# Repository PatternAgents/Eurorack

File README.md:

# EuroRack
EuroRack Specifications and Reference Designs 

-----------------------------------------------------

There are many "patchable" audio synthesizers, including Moog, Buchla, Paia, and many more
from the 1970's and on. Many of those early systems were incompatible with each other,
using different voltage and control levels, so it was difficult to use them together.
Doepfer created the A-100 System, on which Eurorack is based, for a more open
framework where different manufacturers or designers could add modules to the
system to personalize it. EuroRack has become very popular for modular synthesizers. 

This repository contains Open Source Hardware Reference Designs for EuroRack (Legacy 1.0)
that anyone can use or fabricate for themselves.

If you would like to purchase pre-built and tested units,
please see our website at : [PatternAgents](https://patternagents.com/store)

-----------------------------------------------------

EuroRack References and Articles

[Doepfer-Creator](http://www.doepfer.de/a100_man/a100m_e.htm)

[Wikipedia-Doepfer](https://en.wikipedia.org/wiki/Doepfer_A-100)

[Patch Pierre](http://patchpierre.blogspot.com/2012/02/eurorack-standard.html)

[SDIY Info](https://www.sdiy.info/w/Eurorack)

-----------------------------------------------------

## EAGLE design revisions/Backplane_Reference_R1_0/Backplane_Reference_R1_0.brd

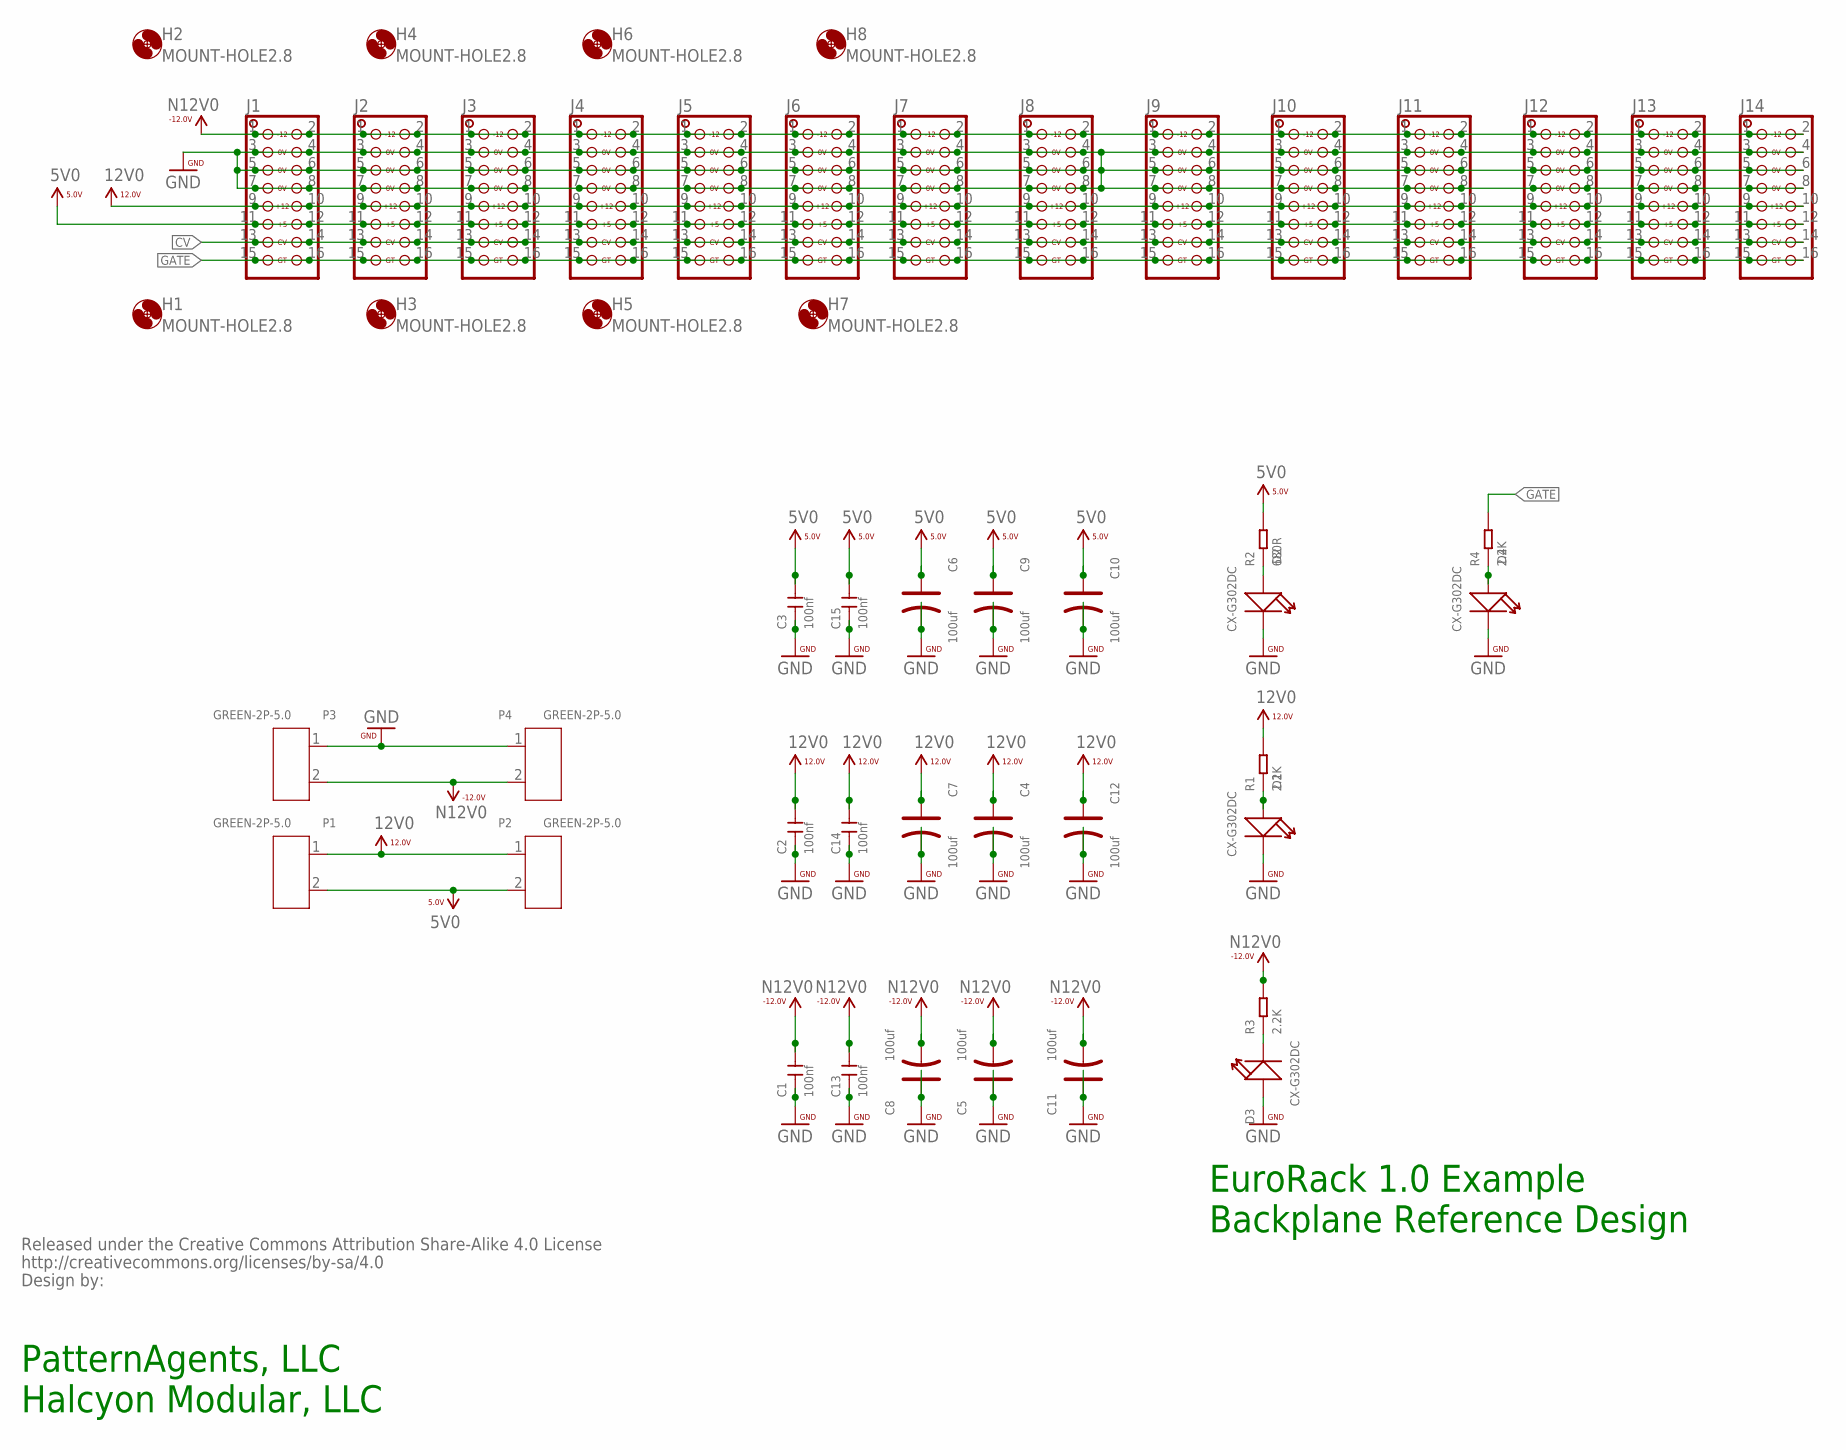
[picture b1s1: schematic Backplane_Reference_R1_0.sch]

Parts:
C1, C2, C3, C13, C14, C15: 100nf; CERAMIC-2.54
C4, C5, C6, C7, C8, C9, C10, C11, C12: 100uf; PC-D5.3MM
D1, D2, D3, D4: CX-G302DC; LED2-2.54-D3.0MM
H1, H2, H3, H4, H5, H6, H7, H8: MOUNT-HOLE2.8; 2,8
J1, J2, J3, J4, J5, J6, J7, J8, J9, J10, J11, J12, J13, J14: EUROPWR_2X08-SHROUD; 2X08_EUROPWR_SHROUD
P1, P2, P3, P4: GREEN-2P-5.0; H2-5.0-10.5X8.0MM
R1, R3, R4: 2.2K; PR-D2.3XL6.5MM
R2: 680R; PR-D2.3XL6.5MM
U$48: BY_CC_SA_TEXTTEXT; BY_CC_SA_TEXT

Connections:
5V0: C3.2, C6.+, C9.+, C10.+, C15.2, J1.11, J1.12, J2.11, J2.12, J3.11, J3.12, J4.11, J4.12, J5.11, J5.12, J6.11, J6.12, J7.11, J7.12, J8.11, J8.12, J9.11, J9.12, J10.11, J10.12, J11.11, J11.12, J12.11, J12.12, J13.11, J13.12, J14.11, J14.12, P1.2, P2.2, R2.2
12V0: C2.2, C4.+, C7.+, C12.+, C14.2, J1.9, J1.10, J2.9, J2.10, J3.9, J3.10, J4.9, J4.10, J5.9, J5.10, J6.9, J6.10, J7.9, J7.10, J8.9, J8.10, J9.9, J9.10, J10.9, J10.10, J11.9, J11.10, J12.9, J12.10, J13.9, J13.10, J14.9, J14.10, P1.1, P2.1, R1.2
CV: J1.13, J1.14, J2.13, J2.14, J3.13, J3.14, J4.13, J4.14, J5.13, J5.14, J6.13, J6.14, J7.13, J7.14, J8.13, J8.14, J9.13, J9.14, J10.13, J10.14, J11.13, J11.14, J12.13, J12.14, J13.13, J13.14, J14.13, J14.14
GATE: J1.15, J1.16, J2.15, J2.16, J3.15, J3.16, J4.15, J4.16, J5.15, J5.16, J6.15, J6.16, J7.15, J7.16, J8.15, J8.16, J9.15, J9.16, J10.15, J10.16, J11.15, J11.16, J12.15, J12.16, J13.15, J13.16, J14.15, J14.16, R4.2
GND: C1.1, C2.1, C3.1, C4.-, C5.+, C6.-, C7.-, C8.+, C9.-, C10.-, C11.+, C12.-, C13.1, C14.1, C15.1, D1.K (-), D2.K (-), D3.A (+), D4.K (-), J1.3, J1.4, J1.5, J1.6, J1.7, J1.8, J2.3, J2.4, J2.5, J2.6, J2.7, J2.8, J3.3, J3.4, J3.5, J3.6, J3.7, J3.8, J4.3, J4.4, J4.5, J4.6, J4.7, J4.8, J5.3, J5.4, J5.5, J5.6, J5.7, J5.8, J6.3, J6.4, J6.5, J6.6, J6.7, J6.8, J7.3, J7.4, J7.5, J7.6, J7.7, J7.8, J8.3, J8.4, J8.5, J8.6, J8.7, J8.8, J9.3, J9.4, J9.5, J9.6, J9.7, J9.8, J10.3, J10.4, J10.5, J10.6, J10.7, J10.8, J11.3, J11.4, J11.5, J11.6, J11.7, J11.8, J12.3, J12.4, J12.5, J12.6, J12.7, J12.8, J13.3, J13.4, J13.5, J13.6, J13.7, J13.8, J14.3, J14.4, J14.5, J14.6, J14.7, J14.8, P3.1, P4.1
N12V0: C1.2, C5.-, C8.-, C11.-, C13.2, J1.1, J1.2, J2.1, J2.2, J3.1, J3.2, J4.1, J4.2, J5.1, J5.2, J6.1, J6.2, J7.1, J7.2, J8.1, J8.2, J9.1, J9.2, J10.1, J10.2, J11.1, J11.2, J12.1, J12.2, J13.1, J13.2, J14.1, J14.2, P3.2, P4.2, R3.2
unnamed: D3.K (-), R3.1
unnamed: D1.A (+), R1.1
unnamed: D2.A (+), R2.1
unnamed: D4.A (+), R4.1

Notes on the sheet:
EuroRack 1.0 Example Backplane Reference Design
PatternAgents, LLC Halcyon Modular, LLC

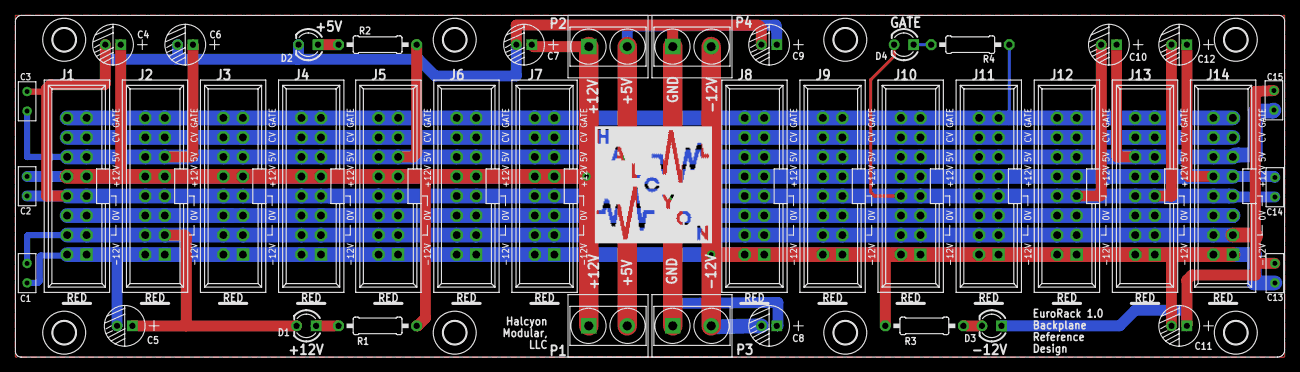
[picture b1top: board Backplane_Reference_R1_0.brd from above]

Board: 2 copper layers, 165.1 x 44.5 mm, 52 parts (1 on the bottom side), 10 nets.

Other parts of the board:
U$19, U$47: HALCYON_DIAGON

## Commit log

2018-01-19 Eurorack Backplane
2018-01-19 initial version

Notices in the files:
parts and their libraries:
PatternAgents-Logos: License : http://creativecommons.org/licenses/by-sa/3.0
(Creative Commons 3.0)
PatternAgents-Logos: Source : http://wiki.creativecommons.org/CC_markers
PatternAgents-Logos: Released under the Creative Commons Attribution Share-Alike 4.0 License
